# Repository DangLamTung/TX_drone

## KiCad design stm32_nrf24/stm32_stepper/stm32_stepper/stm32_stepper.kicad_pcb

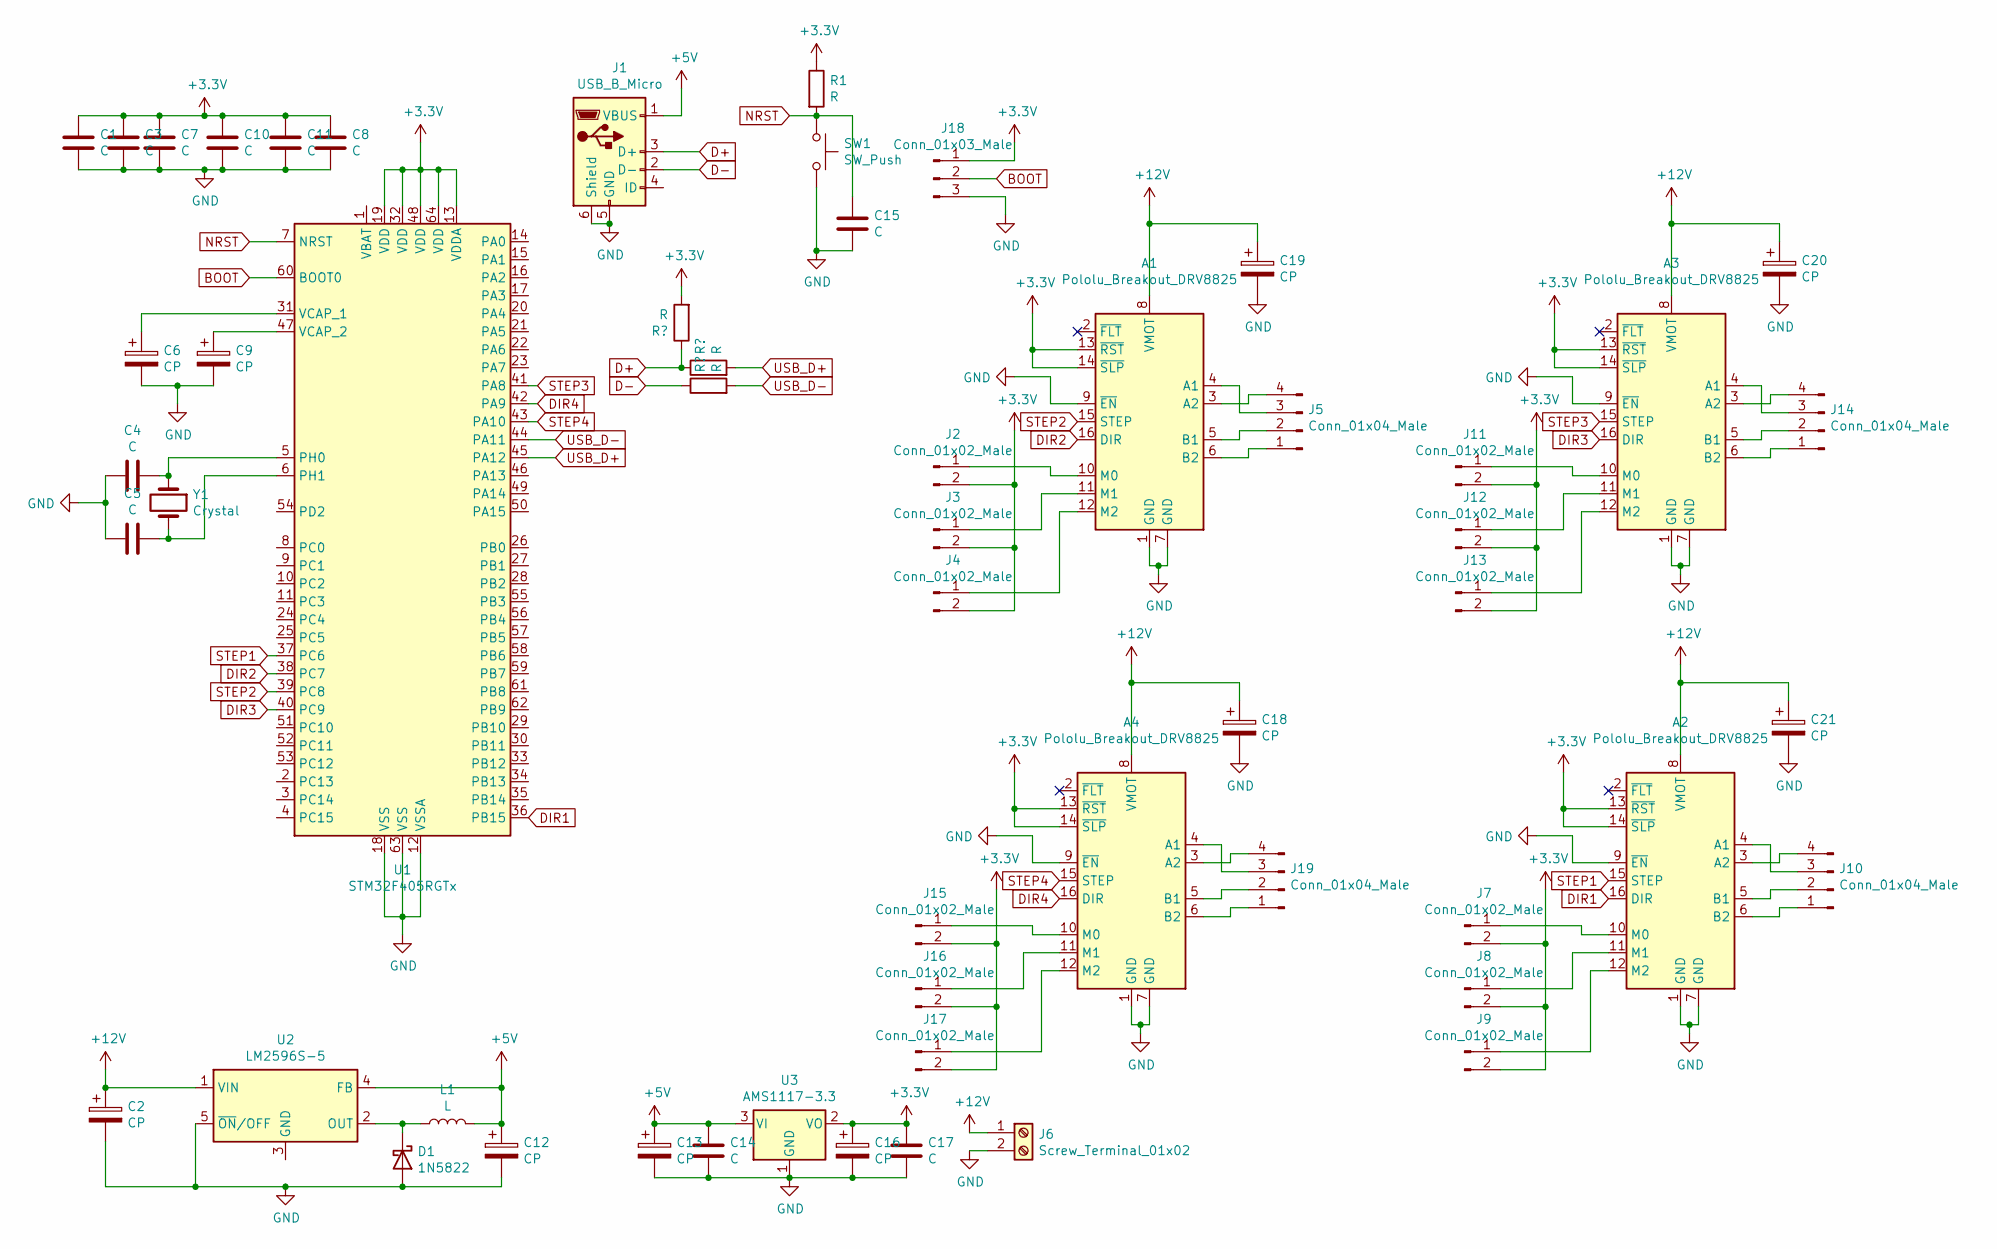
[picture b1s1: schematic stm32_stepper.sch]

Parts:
A1, A2, A3, A4: Pololu_Breakout_DRV8825; Pololu_Breakout-16_15.2x20.3mm
C1, C3, C4, C5, C7, C8, C10, C11, C14, C17: C; C_0603_1608Metric
C2, C12, C18, C19, C20, C21: CP; CP_Elec_5x5.3
C6, C9, C13, C16: CP; CP_EIA-3528-12_Kemet-T_Pad1.50x2.35mm_HandSolder
C15: C
D1: 1N5822; D_DO-201AD_P15.24mm_Horizontal
J1: USB_B_Micro; USB_Micro-B_Amphenol_10103594-0001LF_Horizontal
J2, J3, J4, J7, J8, J9, J11, J12, J13, J15, J16, J17: Conn_01x02_Male; PinSocket_1x02_P2.54mm_Vertical
J5, J10, J14, J19: Conn_01x04_Male; TerminalBlock_4Ucon_1x04_P3.50mm_Vertical
J6: Screw_Terminal_01x02; TerminalBlock_bornier-2_P5.08mm
J18: Conn_01x03_Male; PinSocket_1x03_P2.54mm_Vertical
L1: L; L_6.3x6.3_H3
R1: R; R_0603_1608Metric
SW1: SW_Push
U1: STM32F405RGTx; LQFP-64_10x10mm_P0.5mm
U2: LM2596S-5; TO-263-5_TabPin3
U3: AMS1117-3.3; SOT-223-3_TabPin2
Y1: Crystal; Crystal_SMD_3225-4Pin_3.2x2.5mm_HandSoldering

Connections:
+3V3: A1.13 (~RST), A1.14 (~SLP), A2.13 (~RST), A2.14 (~SLP), A3.13 (~RST), A3.14 (~SLP), A4.13 (~RST), A4.14 (~SLP), C1.1, C3.1, C7.1, C8.1, C10.1, C11.1, C16.1, C17.1, J2.2, J3.2, J4.2, J7.2, J8.2, J9.2, J11.2, J12.2, J13.2, J15.2, J16.2, J17.2, J18.1, R1.1, U1.13 (VDDA), U1.19 (VDD), U1.32 (VDD), U1.48 (VDD), U1.64 (VDD), U3.2 (VO); also elsewhere on the board
+5V: C12.1, C13.1, C14.1, J1.1 (VBUS), L1.2, U2.4 (FB), U3.3 (VI)
+12V: A1.8 (VMOT), A2.8 (VMOT), A3.8 (VMOT), A4.8 (VMOT), C2.1, C18.1, C19.1, C20.1, C21.1, J6.1, U2.1 (VIN)
BOOT: J18.2, U1.60 (BOOT0)
D+: J1.3 (D+); also elsewhere on the board
D-: J1.2 (D-); also elsewhere on the board
DIR1: A2.16 (DIR), U1.36 (PB15)
DIR2: A1.16 (DIR), U1.38 (PC7)
DIR3: A3.16 (DIR), U1.40 (PC9)
DIR4: A4.16 (DIR), U1.42 (PA9)
GND: A1.1 (GND), A1.7 (GND), A1.9 (~EN), A2.1 (GND), A2.7 (GND), A2.9 (~EN), A3.1 (GND), A3.7 (GND), A3.9 (~EN), A4.1 (GND), A4.7 (GND), A4.9 (~EN), C1.2, C2.2, C3.2, C4.2, C5.2, C6.2, C7.2, C8.2, C9.2, C10.2, C11.2, C12.2, C13.2, C14.2, C15.2, C16.2, C17.2, C18.2, C19.2, C20.2, C21.2, D1.2 (A), J1.5 (GND), J1.6 (Shield), J6.2, J18.3, SW1.2, U1.12 (VSSA), U1.18 (VSS), U1.63 (VSS), U2.5 (~ON~/OFF), U3.1 (GND)
NRST: C15.1, R1.2, SW1.1, U1.7 (NRST)
unnamed: A1.3 (A2), J5.4
unnamed: A1.4 (A1), J5.3
unnamed: A1.5 (B1), J5.2
unnamed: A1.6 (B2), J5.1
unnamed: A1.10 (M0), J2.1
unnamed: A1.11 (M1), J3.1
unnamed: A1.12 (M2), J4.1
unnamed: A2.3 (A2), J10.4
unnamed: A2.4 (A1), J10.3
unnamed: A2.5 (B1), J10.2
unnamed: A2.6 (B2), J10.1
unnamed: A2.10 (M0), J7.1
unnamed: A2.11 (M1), J8.1
unnamed: A2.12 (M2), J9.1
unnamed: A3.3 (A2), J14.4
unnamed: A3.4 (A1), J14.3
unnamed: A3.5 (B1), J14.2
unnamed: A3.6 (B2), J14.1
unnamed: A3.10 (M0), J11.1
unnamed: A3.11 (M1), J12.1
unnamed: A3.12 (M2), J13.1
unnamed: A4.3 (A2), J19.4
unnamed: A4.4 (A1), J19.3
unnamed: A4.5 (B1), J19.2
unnamed: A4.6 (B2), J19.1
unnamed: A4.10 (M0), J15.1
unnamed: A4.11 (M1), J16.1
unnamed: A4.12 (M2), J17.1
unnamed: C4.1, U1.5 (PH0), Y1.1
unnamed: C5.1, U1.6 (PH1), Y1.2
unnamed: C6.1, U1.31 (VCAP_1)
unnamed: C9.1, U1.47 (VCAP_2)
unnamed: D1.1 (K), L1.1, U2.2 (OUT)
STEP1: A2.15 (STEP), U1.37 (PC6)
STEP2: A1.15 (STEP), U1.39 (PC8)
STEP3: A3.15 (STEP), U1.41 (PA8)
STEP4: A4.15 (STEP), U1.43 (PA10)
USB_D+: U1.45 (PA12); also elsewhere on the board
USB_D-: U1.44 (PA11); also elsewhere on the board

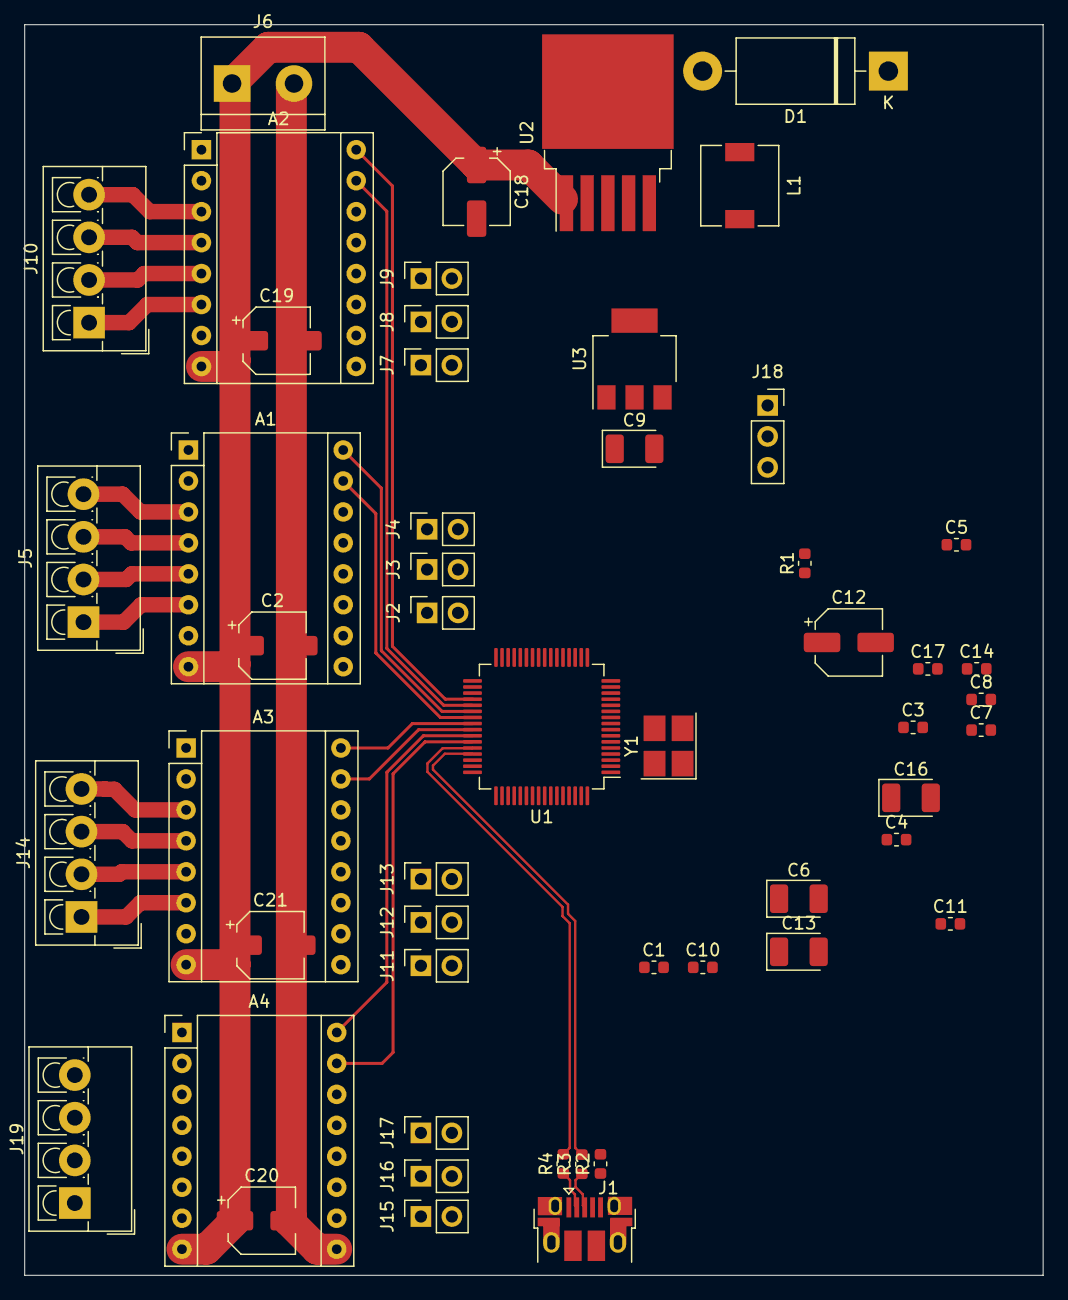
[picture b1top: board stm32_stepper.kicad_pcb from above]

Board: 2 copper layers, 83.6 x 102.6 mm, 53 parts (0 on the bottom side), 51 nets.

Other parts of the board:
R2, R3, R4: R; R_0603_1608Metric

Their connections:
+3V3: R2.2; also elsewhere on the board
D+: R2.1, R3.1; also elsewhere on the board
D-: R4.1; also elsewhere on the board
USB_D+: R3.2; also elsewhere on the board
USB_D-: R4.2; also elsewhere on the board

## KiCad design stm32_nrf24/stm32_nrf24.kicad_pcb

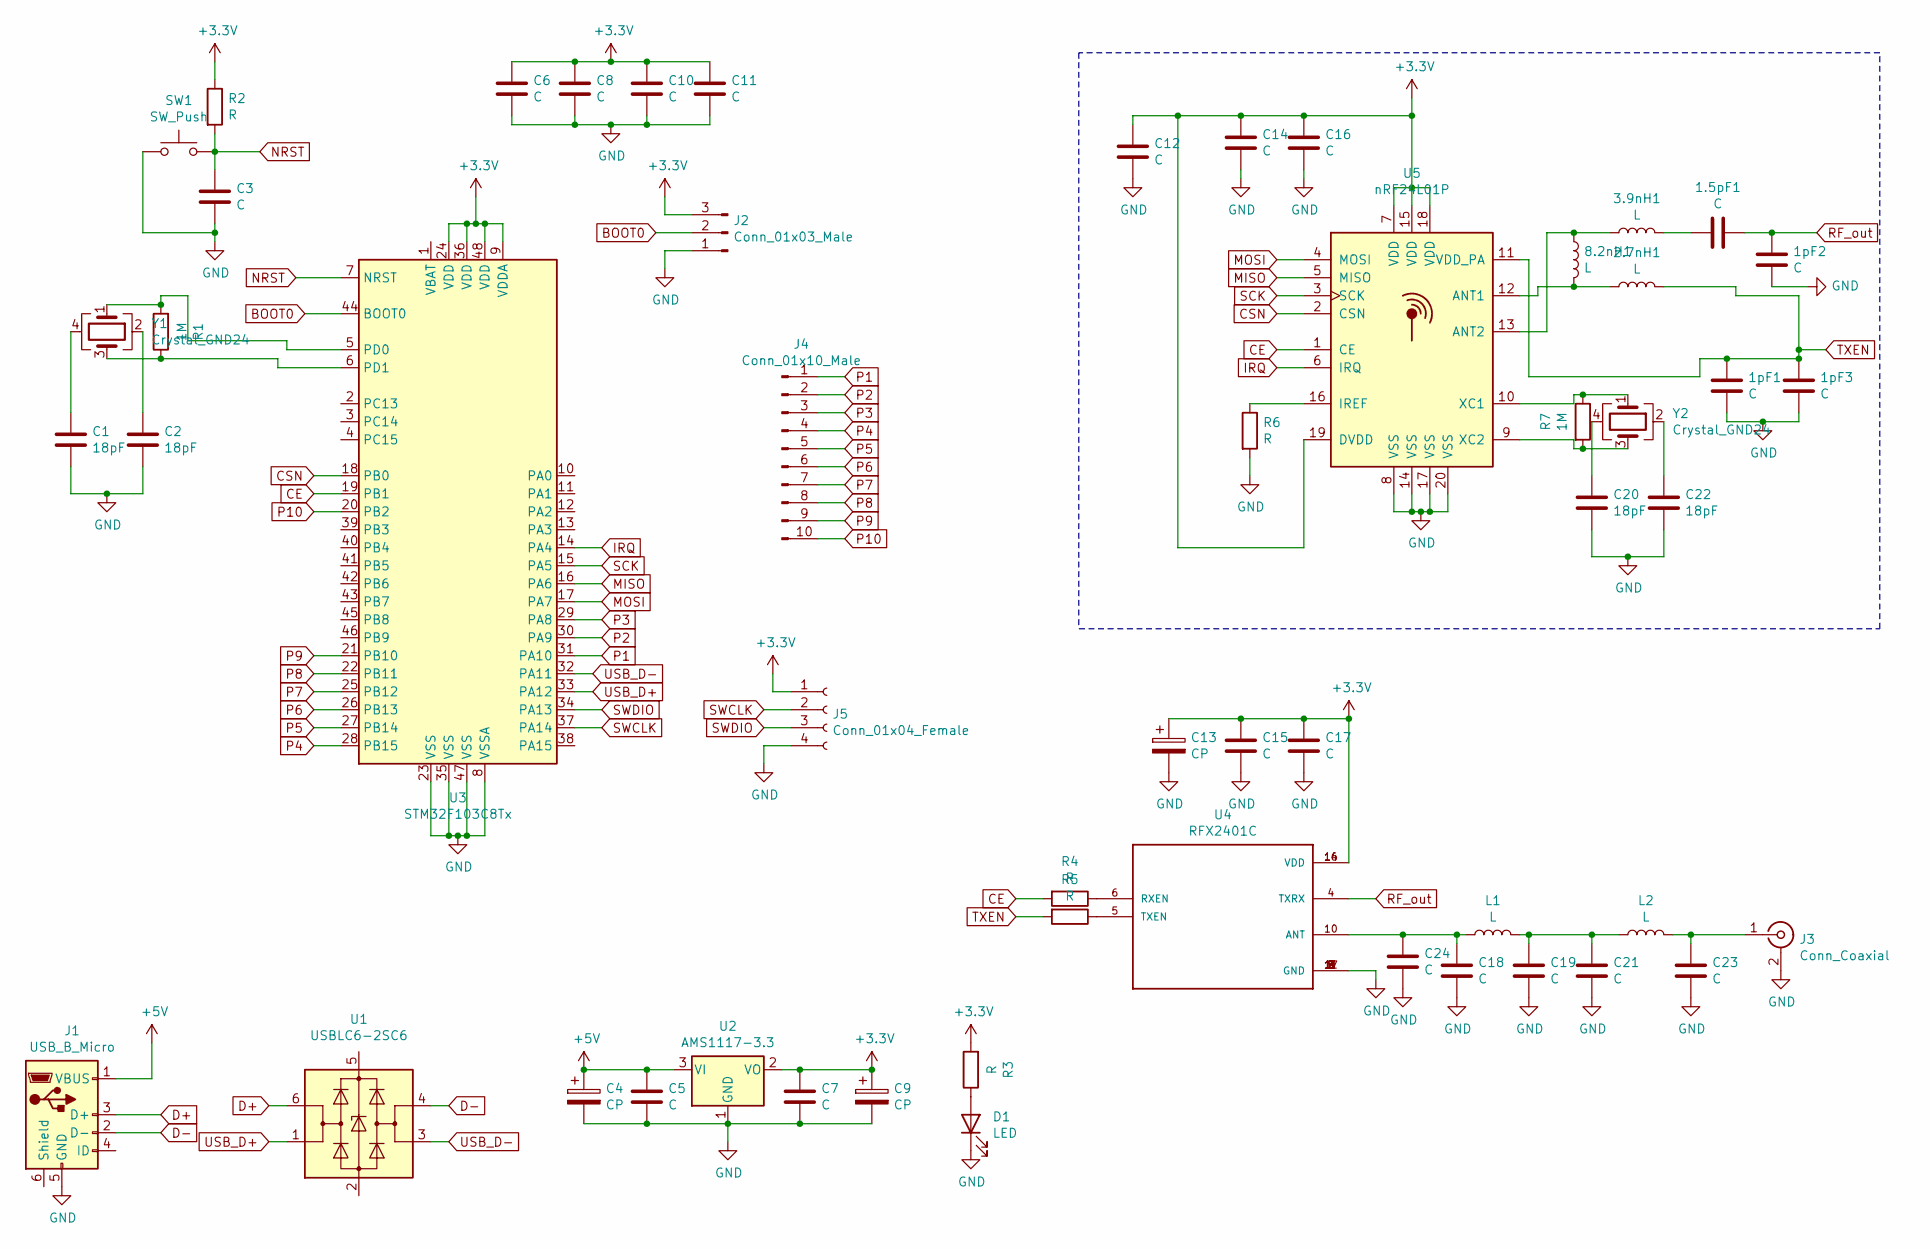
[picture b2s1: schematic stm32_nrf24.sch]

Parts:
1.5pF1, 1pF1, 1pF2, 1pF3: C; C_0603_1608Metric
2.7nH1, 3.9nH1, 8.2nH1: L; C_0603_1608Metric_Pad1.05x0.95mm_HandSolder
C1, C2: 18pF; C_0603_1608Metric_Pad1.05x0.95mm_HandSolder
C3, C5, C6, C7, C8, C10, C11, C14, C15, C16, C17, C18, C19, C21, C23, C24: C; C_0603_1608Metric_Pad1.05x0.95mm_HandSolder
C4, C9, C13: CP; CP_EIA-3528-12_Kemet-T_Pad1.50x2.35mm_HandSolder
C12: C; CP_EIA-3528-12_Kemet-T_Pad1.50x2.35mm_HandSolder
C20, C22: 18pF; C_0603_1608Metric
D1: LED; LED_0603_1608Metric
J1: USB_B_Micro; USB_Micro-B_GCT_USB3076-30-A
J2: Conn_01x03_Male; PinHeader_1x03_P2.54mm_Vertical
J3: Conn_Coaxial; SMA_Amphenol_132289_EdgeMount
J4: Conn_01x10_Male; PinHeader_1x10_P2.54mm_Vertical
J5: Conn_01x04_Female; PinHeader_1x04_P2.54mm_Vertical
L1, L2: L; C_0603_1608Metric_Pad1.05x0.95mm_HandSolder
R1, R7: 1M; R_0603_1608Metric_Pad1.05x0.95mm_HandSolder
R2, R3, R4, R5, R6: R; R_0603_1608Metric_Pad1.05x0.95mm_HandSolder
SW1: SW_Push; SW_PUSH_6mm_H5mm
U1: USBLC6-2SC6; SOT-23-6
U2: AMS1117-3.3; SOT-223-3_TabPin2
U3: STM32F103C8Tx; LQFP-48_7x7mm_P0.5mm
U4: RFX2401C; QFN50P300X300X60-17N
U5: nRF24L01P; QFN-20-1EP_4x4mm_P0.5mm_EP2.5x2.5mm
Y1, Y2: Crystal_GND24; Crystal_SMD_2520-4Pin_2.5x2.0mm

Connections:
+3V3: C6.1, C7.1, C8.1, C9.1, C10.1, C11.1, C12.1, C13.1, C14.1, C15.1, C16.1, C17.1, J2.3, J5.1, R2.1, R3.2, U2.2 (VO), U3.9 (VDDA), U3.24 (VDD), U3.36 (VDD), U3.48 (VDD), U4.14 (VDD), U4.16 (VDD), U5.7 (VDD), U5.15 (VDD), U5.18 (VDD), U5.19 (DVDD)
+5V: C4.1, C5.1, J1.1 (VBUS), U2.3 (VI)
BOOT0: J2.2, U3.44 (BOOT0)
CE: R4.2, U3.19 (PB1), U5.1 (CE)
CSN: U3.18 (PB0), U5.2 (CSN)
D+: J1.3 (D+), U1.6 (I/O1)
D-: J1.2 (D-), U1.4 (I/O2)
GND: 1pF1.2, 1pF2.2, 1pF3.2, C1.2, C2.2, C3.2, C4.2, C5.2, C6.2, C7.2, C8.2, C9.2, C10.2, C11.2, C12.2, C13.2, C14.2, C15.2, C16.2, C17.2, C18.2, C19.2, C20.2, C21.2, C22.2, C23.2, C24.2, D1.1 (K), J1.5 (GND), J2.1, J3.2 (Ext), J5.4, R6.2, SW1.1, U2.1 (GND), U3.8 (VSSA), U3.23 (VSS), U3.35 (VSS), U3.47 (VSS), U4.2 (GND), U4.3 (GND), U4.8 (GND), U4.9 (GND), U4.11 (GND), U4.17 (GND), U5.8 (VSS), U5.14 (VSS), U5.17 (VSS), U5.20 (VSS)
IRQ: U3.14 (PA4), U5.6 (IRQ)
MISO: U3.16 (PA6), U5.5 (MISO)
MOSI: U3.17 (PA7), U5.4 (MOSI)
NRST: C3.1, R2.2, SW1.2, U3.7 (NRST)
unnamed: 1.5pF1.1, 3.9nH1.2
unnamed: 2.7nH1.1, 8.2nH1.2, U5.12 (ANT1)
unnamed: 3.9nH1.1, 8.2nH1.1, U5.13 (ANT2)
unnamed: C1.1, Y1.4
unnamed: C2.1, Y1.2
unnamed: C18.1, C24.1, L1.1, U4.10 (ANT)
unnamed: C19.1, C21.1, L1.2, L2.1
unnamed: C20.1, Y2.4
unnamed: C22.1, Y2.2
unnamed: C23.1, J3.1 (In), L2.2
unnamed: D1.2 (A), R3.1
unnamed: R1.1, U3.6 (PD1), Y1.3
unnamed: R1.2, U3.5 (PD0), Y1.1
unnamed: R4.1, U4.6 (RXEN)
unnamed: R5.1, U4.5 (TXEN)
unnamed: R6.1, U5.16 (IREF)
unnamed: R7.1, U5.10 (XC1), Y2.1
unnamed: R7.2, U5.9 (XC2), Y2.3
P1: J4.1, U3.31 (PA10)
P2: J4.2, U3.30 (PA9)
P3: J4.3, U3.29 (PA8)
P4: J4.4, U3.28 (PB15)
P5: J4.5, U3.27 (PB14)
P6: J4.6, U3.26 (PB13)
P7: J4.7, U3.25 (PB12)
P8: J4.8, U3.22 (PB11)
P9: J4.9, U3.21 (PB10)
P10: J4.10, U3.20 (PB2)
RF_out: 1.5pF1.2, 1pF2.1, U4.4 (TXRX)
SCK: U3.15 (PA5), U5.3 (SCK)
SWCLK: J5.2, U3.37 (PA14)
SWDIO: J5.3, U3.34 (PA13)
TXEN: 1pF1.1, 1pF3.1, 2.7nH1.2, R5.2, U5.11 (VDD_PA)
USB_D+: U1.1 (I/O1), U3.33 (PA12)
USB_D-: U1.3 (I/O2), U3.32 (PA11)

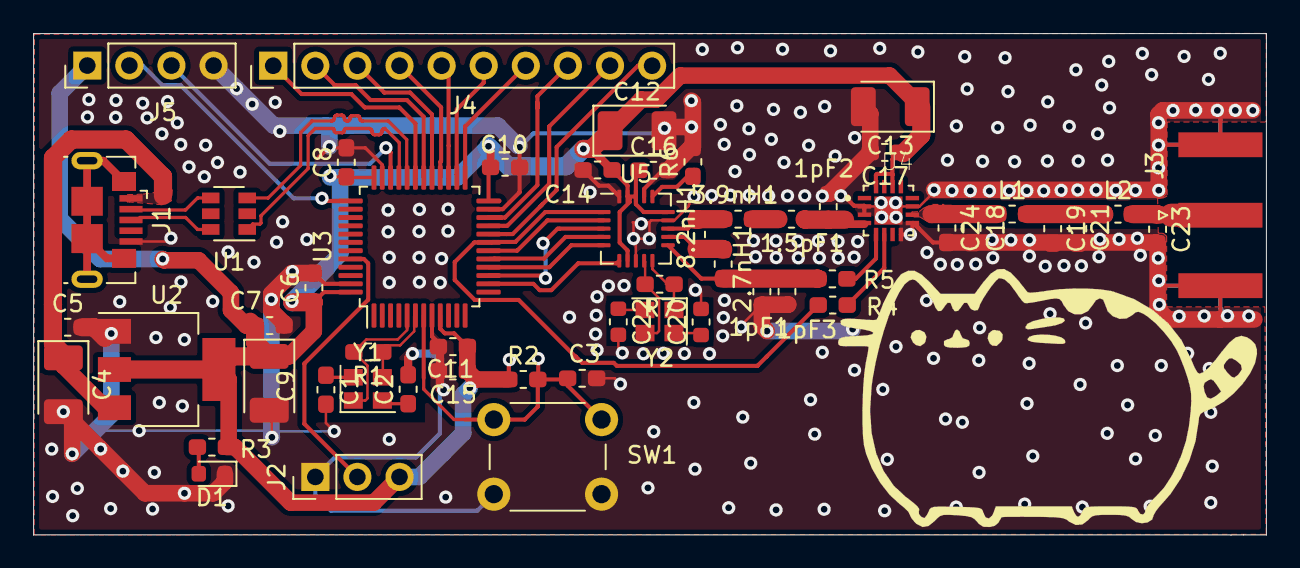
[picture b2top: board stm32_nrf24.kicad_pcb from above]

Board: 2 copper layers, 74.4 x 30.3 mm, 54 parts (0 on the bottom side), 47 nets.

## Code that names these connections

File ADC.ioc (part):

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Mcu.Name=STM32F103C(8-B)Tx
Mcu.Package=LQFP48
Mcu.UserName=STM32F103C8Tx
PA0-WKUP.Signal=ADCx_IN0
PA1.Signal=ADCx_IN1
PA11.Mode=Device
PA11.Signal=USB_DM
PA12.Mode=Device
PA12.Signal=USB_DP
PA13.Mode=Serial_Wire
PA13.Signal=SYS_JTMS-SWDIO
PA14.Mode=Serial_Wire
PA14.Signal=SYS_JTCK-SWCLK
PA2.Signal=ADCx_IN2
PA4.Signal=ADCx_IN4
PA5.Signal=ADCx_IN5
PA6.GPIOParameters=GPIO_PuPd,GPIO_ModeDefaultEXTI
PA6.GPIO_ModeDefaultEXTI=GPIO_MODE_IT_RISING
PA6.GPIO_PuPd=GPIO_PULLUP
PA6.Signal=GPXTI6
PA7.GPIOParameters=GPIO_PuPd,GPIO_ModeDefaultEXTI
PA7.GPIO_ModeDefaultEXTI=GPIO_MODE_IT_RISING
PA7.GPIO_PuPd=GPIO_PULLUP
PA7.Signal=GPXTI7
PA8.GPIOParameters=GPIO_Speed,PinState
PA8.GPIO_Speed=GPIO_SPEED_FREQ_MEDIUM
PA8.PinState=GPIO_PIN_RESET
PA8.Signal=GPIO_Output
PA9.GPIOParameters=GPIO_Speed
PA9.GPIO_Speed=GPIO_SPEED_FREQ_MEDIUM
PA9.Signal=GPIO_Output
PB0.Signal=ADCx_IN8
PB1.Signal=ADCx_IN9
PB13.Mode=Full_Duplex_Master
PB13.Signal=SPI2_SCK
PB14.Mode=Full_Duplex_Master
PB14.Signal=SPI2_MISO
PB15.Mode=Full_Duplex_Master
PB15.Signal=SPI2_MOSI
PB8.Mode=I2C
PB8.Signal=I2C1_SCL
PB9.Mode=I2C
PB9.Signal=I2C1_SDA
PC13-TAMPER-RTC.Signal=GPIO_Output
PD0-OSC_IN.Mode=HSE-External-Oscillator
PD0-OSC_IN.Signal=RCC_OSC_IN
PD1-OSC_OUT.Mode=HSE-External-Oscillator
PD1-OSC_OUT.Signal=RCC_OSC_OUT
RCC.SYSCLKFreq_VALUE=72000000
RCC.SYSCLKSource=RCC_SYSCLKSOURCE_PLLCLK
board=custom

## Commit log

2020-07-24 test
2020-07-31 add alot
2020-08-06 add_pcb
